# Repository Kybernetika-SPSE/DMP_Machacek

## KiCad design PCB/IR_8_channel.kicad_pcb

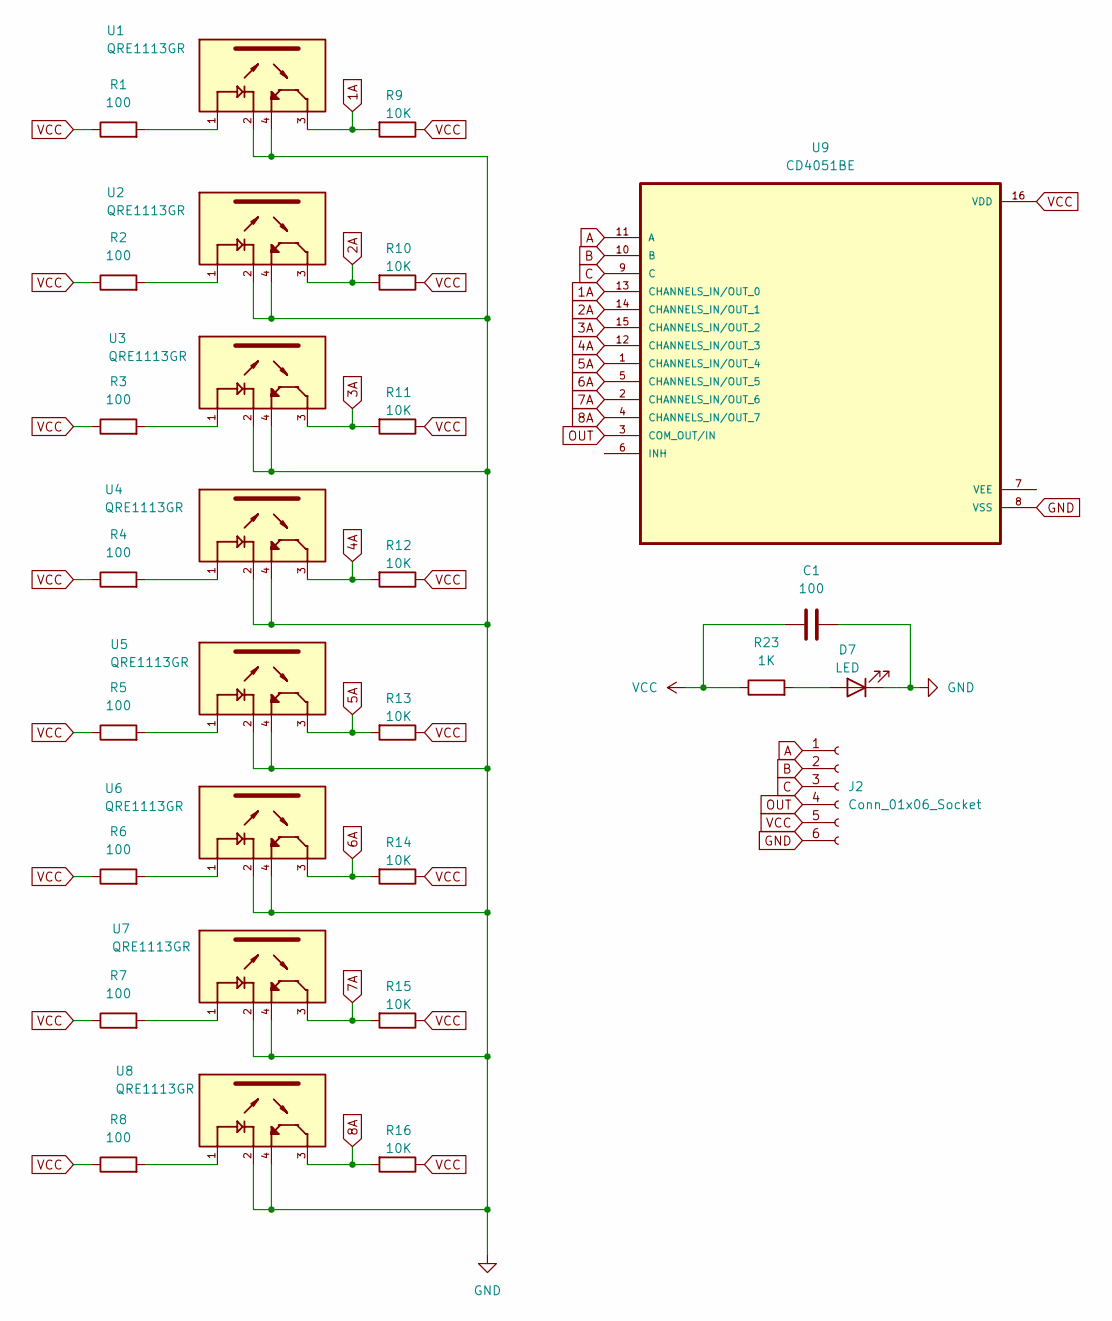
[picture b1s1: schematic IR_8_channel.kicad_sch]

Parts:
C1: 100; CP_Elec_3x5.3
D7: LED; D_0201_0603Metric
J2: Conn_01x06_Socket; JST_XH_S6B-XH-A_1x06_P2.50mm_Horizontal
R1, R2, R3, R4, R5, R6, R7, R8: 100; R_0201_0603Metric
R9, R10, R11, R12, R13, R14, R15, R16: 10K; R_0201_0603Metric
R23: 1K; R_0201_0603Metric
U1, U2, U3, U4, U5, U6, U7, U8: QRE1113GR; SOIC180P460X187-4N; PARTREV 5
U9: CD4051BE; DIP794W45P254L1969H508Q16

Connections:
1A: R9.2, U1.3, U9.13 (CHANNELS_IN/OUT_0)
2A: R10.2, U2.3, U9.14 (CHANNELS_IN/OUT_1)
3A: R11.2, U3.3, U9.15 (CHANNELS_IN/OUT_2)
4A: R12.2, U4.3, U9.12 (CHANNELS_IN/OUT_3)
5A: R13.2, U5.3, U9.1 (CHANNELS_IN/OUT_4)
6A: R14.2, U6.3, U9.5 (CHANNELS_IN/OUT_5)
7A: R15.2, U7.3, U9.2 (CHANNELS_IN/OUT_6)
8A: R16.2, U8.3, U9.4 (CHANNELS_IN/OUT_7)
A: J2.1, U9.11 (A)
B: J2.2, U9.10 (B)
C: J2.3, U9.9 (C)
GND: C1.2, D7.1 (K), J2.6, U1.2, U1.4, U2.2, U2.4, U3.2, U3.4, U4.2, U4.4, U5.2, U5.4, U6.2, U6.4, U7.2, U7.4, U8.2, U8.4, U9.8 (VSS)
unnamed: D7.2 (A), R23.2
unnamed: R1.2, U1.1
unnamed: R2.2, U2.1
unnamed: R3.2, U3.1
unnamed: R4.2, U4.1
unnamed: R5.2, U5.1
unnamed: R6.2, U6.1
unnamed: R7.2, U7.1
unnamed: R8.2, U8.1
OUT: J2.4, U9.3 (COM_OUT/IN)
VCC: C1.1, J2.5, R1.1, R2.1, R3.1, R4.1, R5.1, R6.1, R7.1, R8.1, R9.1, R10.1, R11.1, R12.1, R13.1, R14.1, R15.1, R16.1, R23.1, U9.16 (VDD)

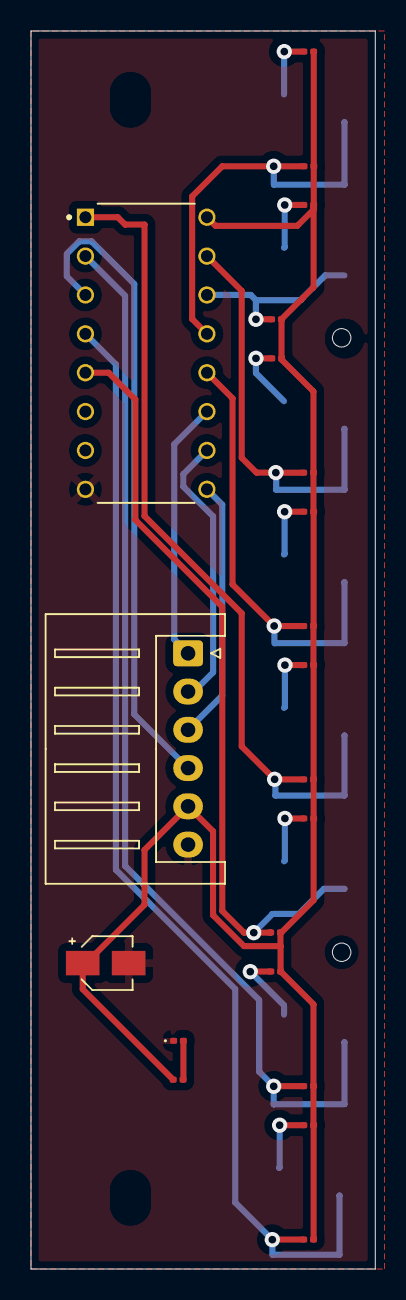
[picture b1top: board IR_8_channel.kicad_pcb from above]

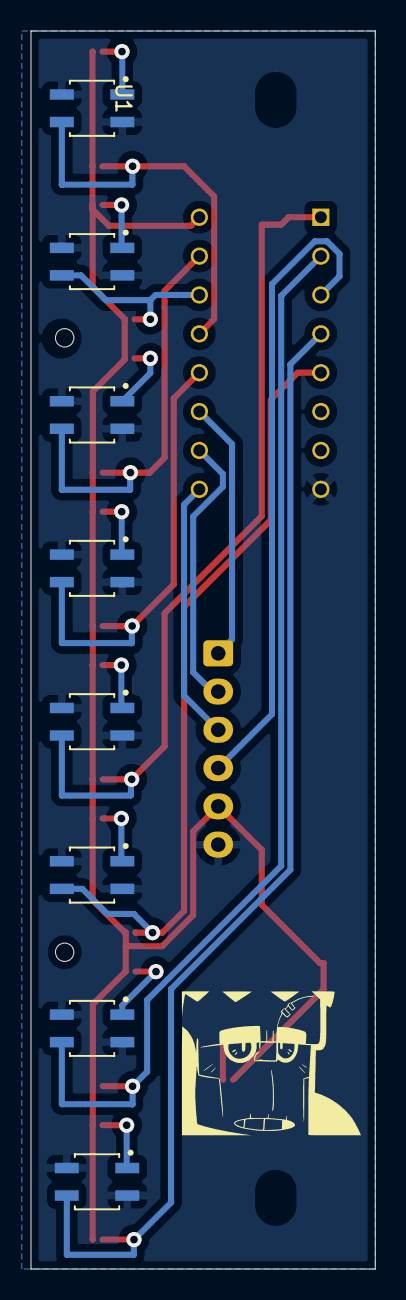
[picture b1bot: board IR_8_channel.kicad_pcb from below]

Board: 2 copper layers, 22.5 x 80.9 mm, 29 parts (8 on the bottom side), 23 nets.

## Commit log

2024-11-21 Create parts
2024-11-21 Create kokot
2024-11-21 Create dd
